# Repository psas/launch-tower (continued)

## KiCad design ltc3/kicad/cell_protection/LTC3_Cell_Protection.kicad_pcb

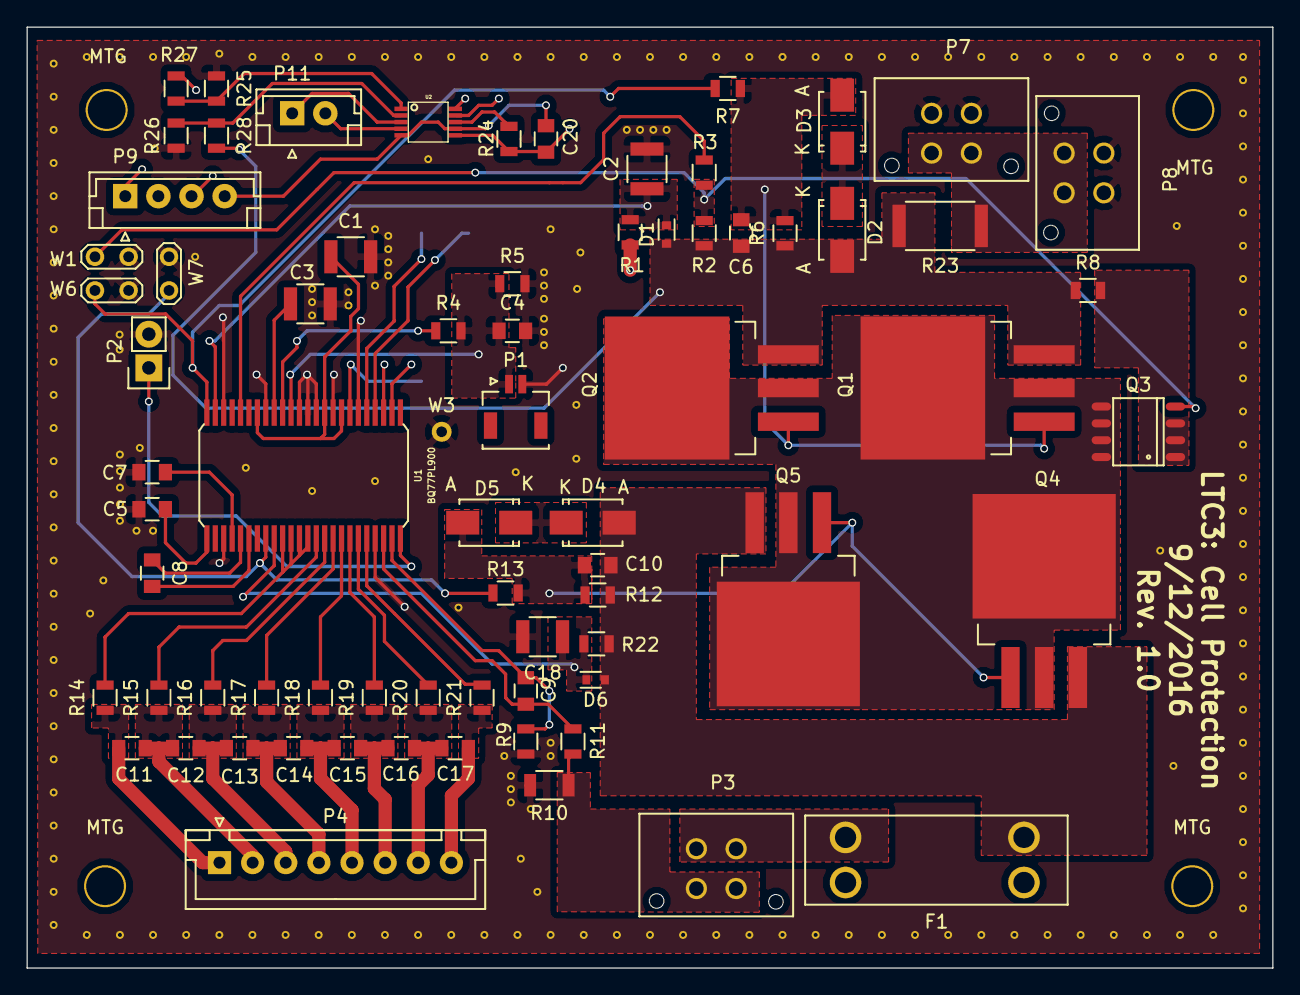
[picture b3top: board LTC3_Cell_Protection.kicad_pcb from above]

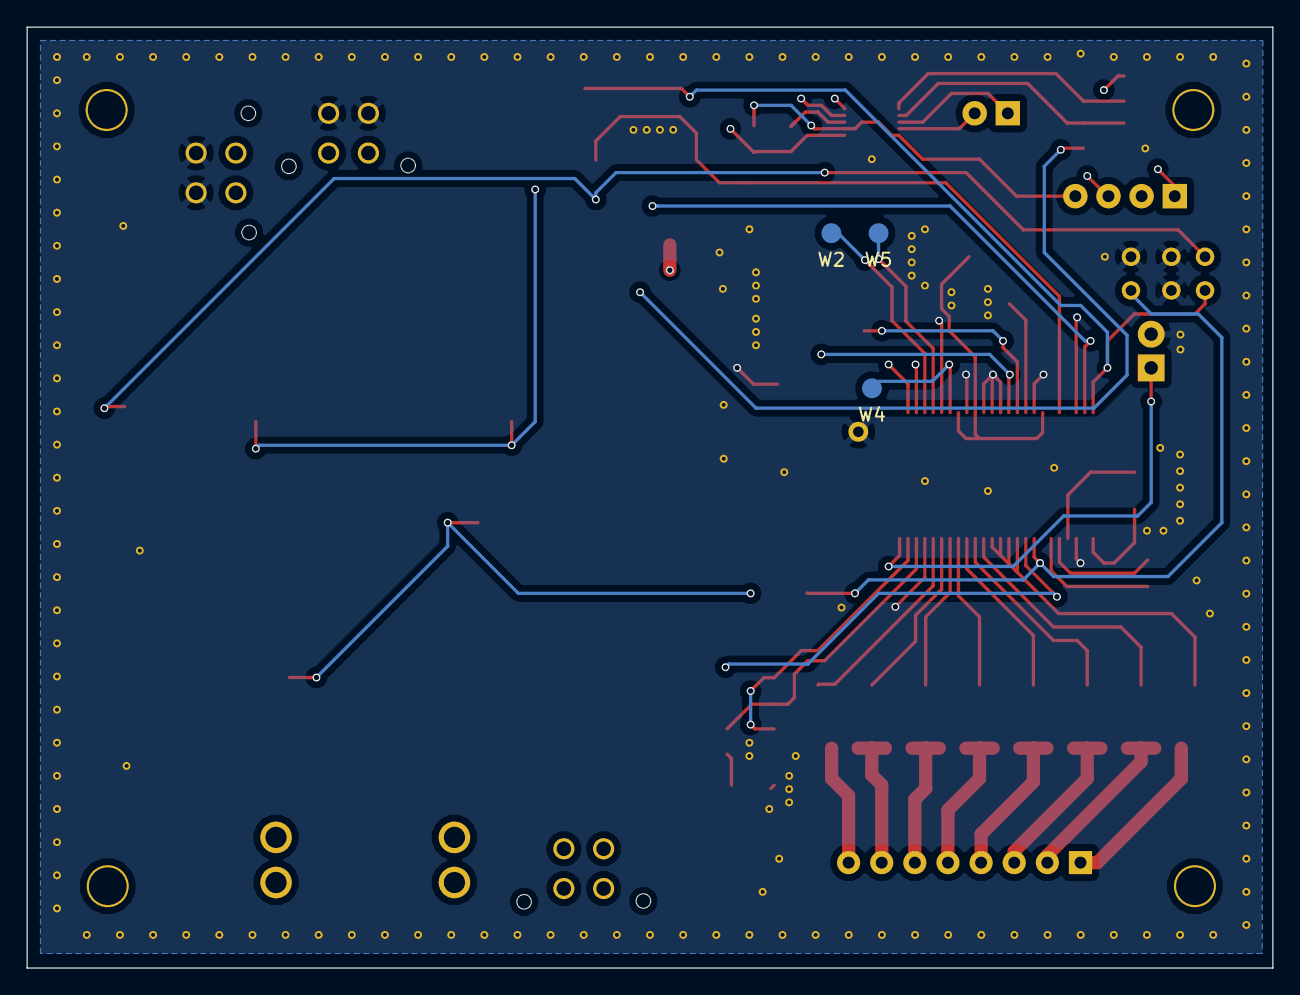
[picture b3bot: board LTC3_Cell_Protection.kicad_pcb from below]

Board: 4 copper layers, 94.0 x 71.0 mm, 80 parts (3 on the bottom side), 57 nets.

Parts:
C1, C2, C3, C18: 2.2μ; C_1210
C4: 10n; C_0805
C5: 4.7μ; C_0805
C6, C10: 4.7n; C_0805
C7, C8: 1μ; C_0805
C9, C11, C12, C13, C14, C15, C16, C17, C20: 0.1μ; C_0805
D1, D6: CDSU4148; SOD-523
D2, D3, D4, D5: SMAZ16; SMA_Standard
F1: 10A; Fuseholder_Auto_Blade_Regular_Keystone_3557-2
MTG: MountingHole_0.1120in_#4; MountingHole_0.1120in_number4
MTG#2, MTG#3, MTG#4: MountingHole_0.1120in_#4; MountingHole_0.1120in_number4
P1: XH header; JST_SHL_SM02B-SHLS-TF_02x1.00mm_Angled
P2: pin header; Pin_Header_Straight_1x02
P3, P7, P8: XH header; Molex_Microfit3_Header_02x02_Straight_43045-0428
P4: XH header; JST_XH_B08B-XH-A_08x2.50mm_Straight
P9: XH header; JST_EH_B04B-EH-A_04x2.50mm_Straight
P11: XH header; JST_EH_B02B-EH-A_02x2.50mm_Straight
Q1, Q2, Q4, Q5: SUM110P08-11; TO-263-3Lead
Q3: NDS9407; SO-8
R1: 10k; R_0805
R2: 390k; R_0805
R3: 820k; R_0805
R4: 6.98k; R_0805
R5: 61.9k; R_0805
R6, R12: 1M; R_0805
R7, R13: 1k; R_0805
R8: 1.78k; R_0805
R9, R11: 200; R_0805
R10: 1m; R_1206
R14, R15, R16, R17, R18, R19, R20, R21: 510; R_0805
R22: 100k; R_0805
R23: 60m; R_2512
R24: 5.6k; R_0805
R25, R26: 12k; R_0805
R27, R28: 75k; R_0805
U1: BQ77PL900
U2: LTC2990; MSOP-10
W1, W6, W7: TEST; Test_Point_2Pads
W2, W4, W5: TEST_1P; Measurement_Point_Round-SMD-Pad_Small
W3: TEST_1P; Measurement_Point_Round-TH_Small

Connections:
/I2C_CLK: P9.2, U1.27, U2.6
/I2C_DATA: P9.3, U1.26, U2.7
/VBATT: P7.3, P7.4, P8.3, P8.4, R1.1, R23.2, R27.2
GND: C1.2, C2.2, C3.2, C4.2, C5.2, C7.2, C18.2, P1.2, P2.2, P7.1, P7.2, P8.1, P8.2, R5.2, R9.2, R10.1, R25.1, R26.1, U1.3, U1.21, U1.30, U1.33, U1.35, U1.36, U1.37, U1.41, U1.46, W1.2, W3.1, W6.2, W7.2
GNDREF: C20.2, P9.4, U2.5, U2.9
unnamed: C1.1, U1.32, U1.34, U1.42
unnamed: C2.1, D1.1, R1.2, U1.47
unnamed: C3.1, U1.40
unnamed: C4.1, P1.1, R4.2, R5.1, U1.38
unnamed: C5.1, U1.1
unnamed: C6.1, D1.2, D2.2, Q1.3, Q2.3, R2.1, R6.1, R8.1, R23.1, R28.2
unnamed: C6.2, D3.2, Q1.1, Q2.1, R6.2, R7.1
unnamed: C7.1, U1.4
unnamed: C8.1, U1.5
unnamed: C8.2, U1.6
unnamed: C9.1, R9.1, U1.23
unnamed: C9.2, R11.1, U1.22
unnamed: C10.1, D4.2, D6.2, F1.1, Q4.3, Q5.3, R12.1, R22.1
unnamed: C10.2, D5.2, Q4.1, Q5.1, R12.2, R13.1
unnamed: C11.1, P4.1, R14.1
unnamed: C11.2, C12.1, P4.2, R15.1
unnamed: C12.2, C13.1, P4.3, R16.1
unnamed: C13.2, C14.1, P4.4, R17.1
unnamed: C14.2, C15.1, P4.5, R18.1
unnamed: C15.2, C16.1, P4.6, R19.1
unnamed: C16.2, C17.1, P4.7, R20.1
unnamed: C17.2, P4.8, R21.1
unnamed: C18.1, D6.1, R22.2, U1.9
unnamed: C20.1, P9.1, R24.1, U2.10
unnamed: D2.1, D3.1
unnamed: D4.1, D5.1
unnamed: F1.2, P3.1, P3.2
unnamed: P2.1, U1.24
unnamed: P3.3, P3.4, R10.2, R11.2
unnamed: P11.1, U2.3
unnamed: P11.2, U2.4
unnamed: Q1.2, Q1.4, Q2.2, Q2.4, Q3.5, Q3.6, Q3.7, Q3.8, Q4.2, Q4.4, Q5.2, Q5.4
unnamed: Q3.1, Q3.2, Q3.3, R8.2
unnamed: Q3.4, R2.2, R3.1, W1.1
unnamed: R3.2, U1.44
unnamed: R4.1, U1.39
unnamed: R7.2, U1.48, W6.1
unnamed: R13.2, U1.8, W7.1
unnamed: R14.2, U1.10, U1.11, U1.12, U1.13
unnamed: R15.2, U1.14
unnamed: R16.2, U1.15
unnamed: R17.2, U1.16
unnamed: R18.2, U1.17
unnamed: R19.2, U1.18
unnamed: R20.2, U1.19
unnamed: R21.2, U1.20
unnamed: R24.2, U2.8
unnamed: R25.2, R27.1, U2.1
unnamed: R26.2, R28.1, U2.2
unnamed: U1.28, W2.1
unnamed: U1.29, W5.1
unnamed: U1.31, W4.1

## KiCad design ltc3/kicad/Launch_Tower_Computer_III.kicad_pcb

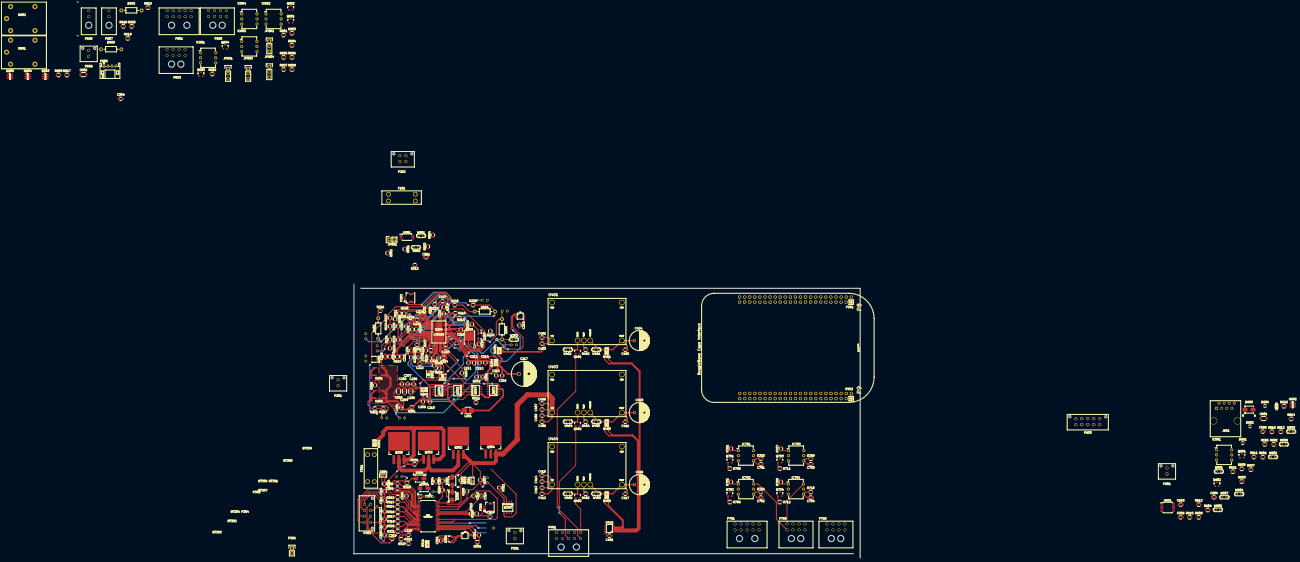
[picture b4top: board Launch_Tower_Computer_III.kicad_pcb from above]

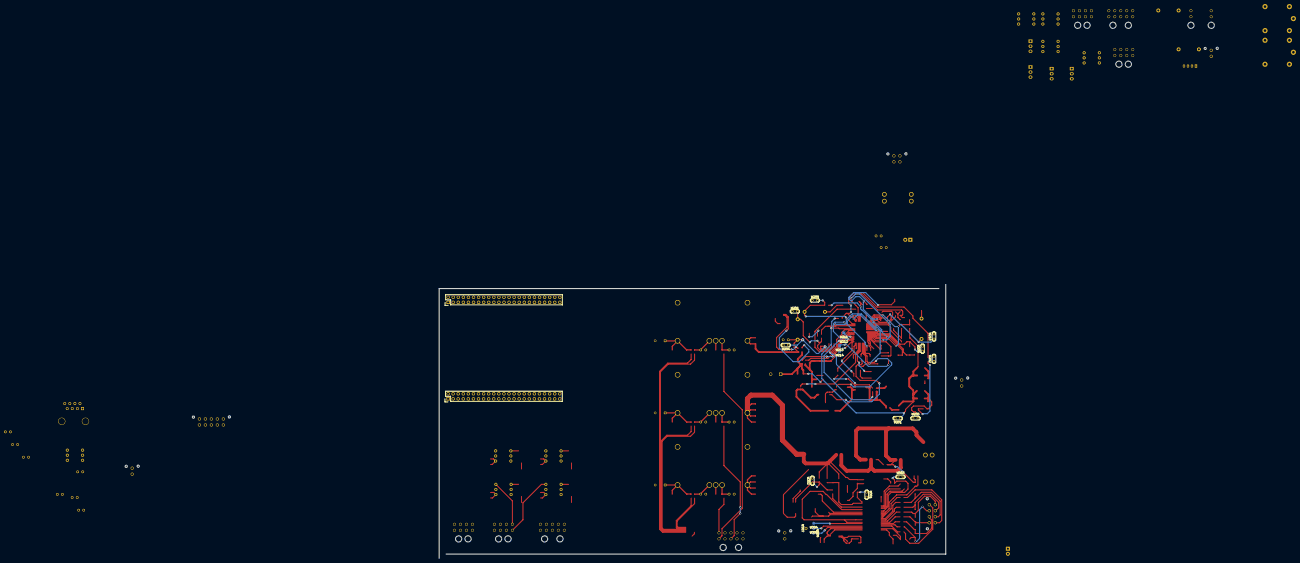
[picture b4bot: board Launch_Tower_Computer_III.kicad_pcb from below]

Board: 2 copper layers, 253.4 x 137.1 mm, 349 parts (21 on the bottom side), 234 nets.

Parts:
BT301, BT302, BT303, BT304, BT305, BT306, BT307, BT308: Dummy_Empty
C201, C202: 470n; C_0805
C203, C204, C205: 33µ; C_1206
C206, C207, C208, C209, C210, C218: 2.2µ; C_0805
C211, C212, C229: 4.7µ; C_0805
C213, C308, C309, C402, C405, C411, C417, C604, C701, C702, C703, C704: 1μ; C_0805
C214, C228, C230: 100n; C_0805
C215, C216: 10μ; C_0805
C217: 150μ; C_Radial_D12.5_L25_P5
C219, C301, C310, C311, C312, C315, C317, C318, C319, C320, C401, C501, C603, C605, C606: 0.1μ; C_0805
C220, C222: 4.7u; C_0805
C221, C225: 1n; C_0805
C223, C224: 220n; C_0805
C226: 0.18µ; C_0805
C227: 1µ; C_0805
C231, C233, C316: 10n; C_0805
C232: 0.33µ; C_0805
C234: 8.2n; C_0805
C235: 220p; C_0805
C236: 68n; C_0805
C302: 470p; C_0805
C303, C304: 4.7n; C_0805
C305, C306, C313, C314, C403: 2.2μ; C_0805
C307, C406, C407, C408, C409, C412, C413, C414, C415: 4.7μ; C_0805
C404, C410, C416: 470μ; C_Radial_D10_L25_P5
C601: 10μ; C_1206
C602: NP; C_1206
D201, D202: CMMR1U-02; SOD-123
D203: 1N4743A; Choke_Horizontal_RM10mm
D204, D205, D603, D605: LED; Choke_Horizontal_RM10mm
D301, D304: 1SS355; TUMD2
D302, D303, D305, D306: SMAZ16; SMA_Standard
D601, D602, D604: CDSU4148; R_0603
D609: 3.3V; SMA_Standard
F201: 15A; Fuseholder_Auto_Blade_Regular_Keystone_3557-2
F301: 10A; Fuseholder_Auto_Blade_Regular_Keystone_3557-2
IC601, IC701, IC702, IC703, IC704, IC801, IC802, IC803, IC804: TLP3542; DIP-6_W7.62mm
J601: RJ45; RJ45_8
JP501: WR_ENABLE; Pin_Header_Straight_1x02
JP801, JP802, JP803, JP804: Trigger Level; Pin_Header_Straight_1x03
K601, K602: RELAY_1C; G5LE-14
L201: 10µH; Inductor_1212
P201: PV_IN; Molex_Microfit3_Header_02x01_Straight_43045-0228
P202: LAB_IN; Molex_Microfit3_Header_02x02_Straight_43045-0428
P203, P305: S2BPHKS; JST_SHL_SM02B-SHLS-TF_02x1.00mm_Angled
P301: CONN_BATT_MAIN; Molex_Microfit3_Header_02x01_Straight_43045-0228
P302, P304: Dummy_Empty
P303: CONN_BATT_SENSE; Molex_Microfit3_Header_02x04_Straight_43045-0828
P306: PIN_HEAD_1x2; Pin_Header_Straight_1x02
P401, P701, P801: 43045-1000; Molex_Microfit3_Header_02x05_Angled_43045-100x
P501: BeagleBone_Black_Expansion_Header_P8; Pin_Header_Straight_2x23
P502: BeagleBone_Black_Expansion_Header_P9; Pin_Header_Straight_2x23
P601: BATT-IN; Molex_Microfit3_Header_02x01_Straight_43045-0228
P603: UMBILICAL; Molex_Microfit3_Header_02x05_Straight_43045-1028
P605, P607: 43045-0200; Molex_Microfit3_Header_02x01_Angled_43045-020x
P606: S4B-PH-K; JST_PH_S4B-PH-K_04x2.00mm_Angled
P608: 43025-0200; Molex_Microfit3_Header_02x01_Straight_43045-0228
P703, P705, P803, P805: 43045-0800; Molex_Microfit3_Header_02x04_Angled_43045-080x
Q201, Q202, Q203, Q204: BSC028N06NS; SO-8
Q205: ZVN4525E6; SOT-26
Q206: ZVP3310F; PG-TDSON-8
Q207: MMBT5550L; SOT-23
Q301: MMBT3904; SOT-23
Q302, Q303, Q304, Q305: SUM110P08-11; TO-263-3Lead
Q306: NDS9407; SO-8
Q401, Q402, Q403: BSS138; SOT-23
Q601, Q602, Q701, Q702, Q703, Q704, Q801, Q802, Q803, Q804: PMV45EN; SOT-23
Q603, Q604, Q605: ZVN4525E6; SOT-23-6
R201, R202, R210, R213: 10; R_0805
R203, R204: 5m; CST0612
R205, R302: 30m; CST0612
R206, R207, R208, R209, R212: 0; R_0805
R211: 5m; R_0805
R214: 196k; R_0805
R215, R217, R236, R303, R601, R605, R608, R615, R622, R705, R706, R711, R712, R803, R804, R807, R808: 10k; R_0805
R216: 8.06k; R_0805
R218, R306, R604, R614: 100k; R_0805
R219: 294k; R_0805
R220, R223: 11.5k; R_0805
R221: 57.6k; R_0805
R222: 10.2k; R_0805
R224: 93.1k; R_0805
R225: 26.1k; R_0805
R226: 215k; R_0805
R227: 7.68k; R_0805
R228: 16.5k; R_0805
R229, R402: 21k; R_0805
R230, R238: 3.32k; R_0805
R231: 27.1k; R_0805
R232: 3.01k; R_0805
R233: 110k; R_0805
R234: 1.3k; R_0805
R235: 243k; R_0805
R237: 53.6k; R_0805
R239: 35.7k; R_0805
R240, R241: 549; R_0805
R242: 200k; R_0805
R301, R501, R502, R503, R504, R612: 5.6k; R_0805
R304, R305: 1M; R_0805
R307: 390k; R_0805
R308: 820k; R_0805
R309, R310: 1k; R_0805
R311: 1.78k; R_0805
R312, R313, R314, R316, R317, R319, R320, R321: 500; R_0805
R315: 6.89k; R_0805
R318: 61.9k; R_0805
R322, R323: 200; R_0805
R324: 1m; CST0612
R401: 0.1; CST0612
R403, R405: 60m; CST0612
R404, R406: 2.91k; R_0805
R602: 120; R_0805
R603, R611: 62k; R_0805
R606: 100; R_0805
R607: 500k; R_0805
R609: NP; R_0805
R610, R620: 250; R_0805
R613: 1.5k; R_0805
R616, R621: 5.1k; R_0805
R617, R618, R619: 30k; R_0805
R701, R702, R707, R708, R801, R802, R805, R806: 270; R_0805
R703, R704, R709, R710: 51k; R_0805
U201, U202: PI2127; LGA-17
U203, U301: LTC2990; MSOP-10
U204: LT8490
U302: BQ77PL900
U401: PTN78020W
U402: LTC2991; MSOP-16
U403, U404: PTN78020H; PTN78020W
U501: 24C256; TSSOP-8_4.4x3mm_Pitch0.65mm
U601: CD74HC14; TSSOP-14_4.4x5mm_Pitch0.65mm
U602: SN65220DBV; SOT-23-6
U603: 741G08; SOT-353
W201, W202, W203, W204, W205, W206, W208, W209, W210, W301, W302, W303, W401, W402, W403, W404, W405, W406, W501, W502: TEST; Test_Point_2Pads
W211, W212, W213, W214: TEST_1P; Measurement_Point_Square-SMD-Pad_Small
W304, W305, W306: TEST_1P; Measurement_Point_Round-SMD-Pad_Small
W307: TEST_1P; Measurement_Point_Round-TH_Small
W601: 14.8-16.8V; Test_Point_2Pads
W602, W603, W604, W605, W606: 0/5V; Test_Point_2Pads
W607: 0/3.3V; Test_Point_2Pads

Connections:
+3V3: C227.1, C229.1, P401.2, P401.5, P401.8, R223.1, R234.1, R238.1, U204.4, U204.14, U204.58
+5V: C219.1, C301.1, C401.1, C501.1, C605.1, C606.1, D601.1, D604.1, JP801.1, JP802.1, JP803.1, JP804.1, P502.5, P502.6, Q603.1, Q604.1, Q605.1, R301.1, R401.1, R501.1, R502.1, R503.1, R504.1, R601.1, R616.1, R701.1, R702.1, R707.1, R708.1, R801.1, R802.1, R805.1, R806.1, U203.10, U301.10, U401.5, U402.16, U501.8, U601.14, W401.2
+12V: P705.1, P705.3, P705.5, P705.7, R403.1, U403.5, W403.2
+19V: P603.1, R405.1, R612.2, U404.5, W405.2
/12V_ENn: P401.4, P502.23
/19V_ENn: P401.7, P502.27
/BeagleBone Black Cape/BQ_XALERT: P501.23, U302.25
/BeagleBone Black Cape/ROCKET_IGNITE: P502.15, Q602.1, R620.1, R622.1, W607.1
/DC-DC Converters/5V_INHIBIT_FET: P401.1, Q401.1
/DC-DC Converters/12V_INHIBIT_FET: P401.3, Q402.1
/DC-DC Converters/19V_INHIBIT_FET: P401.6, Q403.1
/EXT_TRG_EN_1: P501.35, Q801.1, R803.1
/EXT_TRG_EN_2: P501.33, Q802.1, R804.1
/EXT_TRG_EN_3: P501.31, Q803.1, R807.1
/EXT_TRG_EN_4: P501.32, Q804.1, R808.1
/External Device Power/EXT_POW_1_FET_D: P701.1, Q701.3
/External Device Power/EXT_POW_1_LED_CATH: IC701.2, P701.2
/External Device Power/EXT_POW_1_OPTO_RELAY_P: IC701.6, P705.2
/External Device Power/EXT_POW_2_FET_D: P701.3, Q702.3
/External Device Power/EXT_POW_2_LED_CATH: IC702.2, P701.4
/External Device Power/EXT_POW_2_OPTO_RELAY_P: IC702.6, P705.4
/External Device Power/EXT_POW_3_FET_D: P701.5, Q703.3
/External Device Power/EXT_POW_3_LED_CATH: IC703.2, P701.6
/External Device Power/EXT_POW_3_OPTO_RELAY_P: IC703.6, P705.6
/External Device Power/EXT_POW_4_FET_D: P701.7, Q704.3
/External Device Power/EXT_POW_4_LED_CATH: IC704.2, P701.8
/External Device Power/EXT_POW_4_OPTO_RELAY_P: IC704.6, P705.8
/External Device Triggers/EXT_TRG_1_FET_D: P801.1, Q801.3
/External Device Triggers/EXT_TRG_1_LED_CATH: IC801.2, P801.2
/External Device Triggers/EXT_TRG_1_OPTO_RELAY: IC801.6, P803.2
/External Device Triggers/EXT_TRG_2_FET_D: P801.3, Q802.3
/External Device Triggers/EXT_TRG_2_LED_CATH: IC802.2, P801.4
/External Device Triggers/EXT_TRG_2_OPTO_RELAY: IC802.6, P803.4
/External Device Triggers/EXT_TRG_3_FET_D: P801.5, Q803.3
/External Device Triggers/EXT_TRG_3_LED_CATH: IC803.2, P801.6
/External Device Triggers/EXT_TRG_3_OPTO_RELAY: IC803.6, P803.6
/External Device Triggers/EXT_TRG_4_FET_D: P801.7, Q804.3
/External Device Triggers/EXT_TRG_4_LED_CATH: IC804.2, P801.8
/External Device Triggers/EXT_TRG_4_OPTO_RELAY: IC804.6, P803.8
/GPIO_EXT_PWR_1: Q701.1, R705.1
/GPIO_EXT_PWR_2: Q702.1, R706.1
/GPIO_EXT_PWR_3: Q703.1, R711.1
/GPIO_EXT_PWR_4: Q704.1, R712.1
/I2C_CLOCK: P502.19, R503.2, U203.7, U301.7, U302.27, U402.11, U501.6, W502.1
/I2C_DATA: P502.20, R504.2, U203.6, U301.6, U302.26, U402.10, U501.5, W501.1
/IGN_RTL: P501.22, P501.29, R611.2, R614.1
/Power In, Charge Controller/BG1: Q203.4, U204.23
/Power In, Charge Controller/BG2: Q204.4, R208.1
/Power In, Charge Controller/EXTVCC: C202.2, C211.1, C212.1, C213.1, C214.1, Q202.5, R204.2, U204.40
/Power In, Charge Controller/SW1: C223.1, L201.1, Q201.3, Q203.5, U204.31
/Power In, Charge Controller/SW2: C224.1, L201.2, Q202.3, Q204.5, U204.29
/Power In, Charge Controller/TG1: Q201.4, R207.2
/Power In, Charge Controller/TG2: Q202.4, U204.28
/ROCKET_READYn: P501.25, R603.1, R604.2
/Rocket Umbilical & Ignition Control/IGN_BATT_P: P601.1, W601.2
/Rocket Umbilical & Ignition Control/ROCKET_ETH_1: J601.3, P603.3
/Rocket Umbilical & Ignition Control/ROCKET_ETH_2: J601.4, P603.4
/Rocket Umbilical & Ignition Control/ROCKET_ETH_3: J601.5, P603.5
/Rocket Umbilical & Ignition Control/ROCKET_ETH_4: J601.6, P603.6
/Rocket Umbilical & Ignition Control/ROCKET_READY_5V: P603.2, R602.2, U602.4, U602.6, W602.1
/Rocket Umbilical & Ignition Control/UMB_CONN_FROM_RKT: D609.1, P603.7, R621.2
/UMB_CONn: C604.1, P501.24, P501.27, R616.2, R621.1
GND: C203.2, C204.2, C205.2, C206.2, C207.2, C208.2, C209.2, C210.2, C211.2, C212.2, C213.2, C214.2, C215.2, C216.2, C217.2, C218.2, C219.2, C220.2, C221.2, C222.2, C225.2, C226.2, C227.2, C228.2, C229.2, C230.2, C231.2, C232.2, C233.2, C234.2, C235.2, C236.2, C301.2, C305.2, C306.2, C307.2, C308.2, C313.2, C314.2, C316.2, C401.2, C402.2, C403.2, C404.2, C405.2, C406.2, C407.2, C408.2, C409.2, C410.2, C411.2, C412.2, C413.2, C414.2, C415.2, C416.2, C417.2, C501.2, C601.2, C602.2, C603.2, C604.2, C605.2, C606.2, C701.2, C702.2, C703.2, C704.2, D603.1, D605.1, D609.2, IC601.2, IC601.4, JP501.2, JP801.3, JP802.3, JP803.3, JP804.3, P201.1, P202.1, P203.2, P305.2, P306.2, P401.9, P401.10, P501.1, P501.2, P502.1, P502.2, P502.43, P502.44, P502.45, P502.46, P603.8, P603.9, P603.10, P606.4, P701.9, P701.10, P703.2, P703.4, P703.6, P703.8, P801.9, P801.10, P805.2, P805.4, P805.6, P805.8, Q205.4, Q401.2, Q402.2, Q403.2, Q601.2, Q602.2, Q701.2, Q702.2, Q703.2, Q704.2, Q801.2, Q802.2, Q803.2, Q804.2, R206.2, R211.2, R212.2, R213.2, R216.2, R217.2, R222.2, R225.2, R226.1, R227.2, R229.2, R235.2, R239.2, R240.2, R241.2, R242.2, R318.2, R324.1, R402.2, R404.2, R406.2, R604.1, R605.2, R608.2, R613.2, R614.2, R615.2, R617.2, R618.2, R619.2, R622.2, R703.2, R704.2, R705.2, R706.2, R709.2, R710.2, R711.2, R712.2, R803.2, R804.2, R807.2, R808.2, U201.6, U202.6, U203.5, U203.8, U203.9, U204.9, U204.21, U204.55, U204.59, U204.61, U204.62, U204.63, U301.5, U301.9, U302.3, U302.21, U302.30, U302.33, U302.35, U302.36, U302.37, U302.41, U302.46, U401.1, U401.7, U402.9, U402.13, U402.14, U402.15, U403.1, U403.7, U404.1, U404.7, U501.1, U501.2, U501.4, U601.7, U602.2, U602.5, W201.2, W202.2, W203.2, W204.2, W205.1, W206.2, W208.2, W209.2, W210.2, W301.2, W302.2, W303.2, W307.1, W401.1, W402.1, W403.1, W404.1, W405.1, W406.1, W501.2, W502.2, W602.2, W603.2, W604.2, W605.2, W606.2, W607.2
GND_IGN: P601.2, P607.2, W601.1
unnamed: C201.1, R201.2
unnamed: C202.1, R202.2
unnamed: C209.1, C210.1, Q201.5, R201.1, R203.1
unnamed: C215.1, C216.1, C217.1, R202.1, R204.1, R205.2
unnamed: C220.1, C222.1, R209.1, U204.7, U204.24
unnamed: C221.1, R210.1, U204.13
unnamed: C223.2, D201.1, U204.33
unnamed: C224.2, D202.1, U204.27
unnamed: C225.1, R213.1, U204.12
unnamed: C226.1, R220.1, R221.2
unnamed: C228.1, U204.19
unnamed: C230.1, P203.1, R223.2, U204.3
unnamed: C231.1, R229.1, U204.10, U204.53
unnamed: C232.1, R228.2, R230.2
unnamed: C233.1, R231.2, R232.2, R235.1, U204.17
unnamed: C234.1, R236.2
unnamed: C235.1, R236.1, U204.18
unnamed: C236.1, R237.2, U204.56
unnamed: C302.1, Q301.1, Q301.2, U301.3
unnamed: C302.2, Q301.3, U301.4
unnamed: C303.2, D305.2, Q302.1, Q304.1, R304.2, R309.1
unnamed: C304.1, D303.2, D304.2, Q303.3, Q305.3, R302.2, R305.1, R306.1
unnamed: C304.2, D306.2, Q303.1, Q305.1, R305.2, R310.1
unnamed: C305.1, D301.1, R303.2, U302.47
unnamed: C306.1, D304.1, R306.2, U302.9
unnamed: C307.1, U302.1
unnamed: C308.1, U302.4
unnamed: C309.1, U302.5
unnamed: C309.2, U302.6
unnamed: C310.1, P303.1, R312.1
unnamed: C310.2, C311.1, P303.2, R313.1
unnamed: C311.2, C312.1, P303.3, R314.1
unnamed: C312.2, C315.1, P303.4, R316.1
unnamed: C313.1, U302.32, U302.34, U302.42
unnamed: C314.1, U302.40
unnamed: C315.2, C317.1, P303.5, R317.1
unnamed: C316.1, P305.1, R315.2, R318.1, U302.38
unnamed: C317.2, C318.1, P303.6, R319.1
unnamed: C318.2, C319.1, P303.7, R320.1
unnamed: C319.2, P303.8, R321.1
unnamed: C320.1, R322.1, U302.22
unnamed: C320.2, R323.1, U302.23
unnamed: C404.1, C405.1, R401.2, U401.6
unnamed: C410.1, C411.1, R403.2, U403.6
unnamed: C416.1, C417.1, R405.2, U404.6
unnamed: C601.1, C602.1, R606.1, R607.1, R609.1, U601.9, W606.1
unnamed: C603.1, R612.1, R613.1, U601.13, W603.1
unnamed: C701.1, IC701.4, P703.1, R703.1
unnamed: C702.1, IC702.4, P703.3, R704.1
unnamed: C703.1, IC703.4, P703.5, R709.1
unnamed: C704.1, IC704.4, P703.7, R710.1
unnamed: D201.2, D202.2, R209.2
unnamed: D203.2, Q206.2, Q207.2, R218.2, W206.1
unnamed: D204.1, R240.1
unnamed: D204.2, R234.2, U204.51, W209.1
unnamed: D205.1, R241.1
unnamed: D205.2, R238.2, U204.2, W210.1
unnamed: D302.1, D305.1
unnamed: D303.1, D306.1
unnamed: D601.2, Q601.3
unnamed: D602.1, R607.2, R609.2, U603.3
unnamed: D602.2, R606.2
unnamed: D603.2, R610.2
unnamed: D604.2, Q602.3
unnamed: D605.2, R620.2
unnamed: F201.1, P202.2
unnamed: F201.2, R215.1, U202.12, U202.13, U202.14, U202.15, U202.16, W205.2
unnamed: F301.1, R302.1
unnamed: F301.2, P301.1
unnamed: IC601.1, R602.1
unnamed: IC601.6, R601.2, U601.1
unnamed: IC701.1, R701.2
unnamed: IC702.1, R702.2
unnamed: IC703.1, R707.2
unnamed: IC704.1, R708.2
unnamed: IC801.1, R801.2
unnamed: IC801.4, P805.1
unnamed: IC802.1, R802.2
unnamed: IC802.4, P805.3
unnamed: IC803.1, R805.2
unnamed: IC803.4, P805.5
unnamed: IC804.1, R806.2
unnamed: IC804.4, P805.7
unnamed: JP501.1, R501.2, U501.7
unnamed: JP801.2, P803.1
unnamed: JP802.2, P803.3
unnamed: JP803.2, P803.7
unnamed: JP804.2, P803.5
unnamed: Q603.3, R617.1
unnamed: P605.1, Q604.3, R618.1
unnamed: P201.2, U201.12, U201.13, U201.14, U201.15, U201.16, W202.1
unnamed: P301.2, R324.2
unnamed: P306.1, U302.24
unnamed: P605.2, P607.1, Q605.3, R619.1
unnamed: P606.1, Q603.4
unnamed: P606.2, Q604.4
unnamed: P606.3, Q605.4
unnamed: Q203.3, Q204.3, R210.2, R211.1
unnamed: Q205.1, R214.2, R216.1, U204.54
unnamed: Q205.3, R215.2, R217.1
unnamed: Q206.1, R219.1
unnamed: Q207.1, R242.1, U204.8, U204.49
unnamed: Q207.3, R225.1
unnamed: Q302.2, Q303.2, Q304.2, Q305.2, Q306.5
unnamed: Q306.3, R311.2
unnamed: Q306.4, R307.2, R308.1, W302.1
unnamed: Q401.3, U401.3, W402.2
unnamed: Q402.3, U403.3, W404.2
unnamed: Q403.3, U404.3, W406.2
unnamed: Q601.1, R608.1, U601.6
unnamed: R203.3, U204.44
unnamed: R203.4, U204.45
unnamed: R204.3, U204.41
unnamed: R204.4, U204.42
unnamed: R205.3, U203.2
unnamed: R205.4, U203.1
unnamed: R206.1, U201.2
unnamed: R207.1, U204.32
unnamed: R208.2, U204.25
unnamed: R212.1, U202.2
unnamed: R219.2, R221.1, R222.1, U204.16, U204.57
unnamed: R220.2, U204.5
unnamed: R224.2, R227.1, R228.1, U204.1, U204.15
unnamed: R226.2, U204.22
unnamed: R230.1, U204.6
unnamed: R231.1, U204.50
unnamed: R232.1, U204.64
unnamed: R233.2, R239.1, U204.11, W208.1
unnamed: R237.1, U204.20
unnamed: R301.2, U301.8
unnamed: R302.3, U301.2
unnamed: R302.4, U301.1
unnamed: R308.2, U302.44
unnamed: R309.2, U302.48, W301.1
unnamed: R310.2, U302.8, W303.1
unnamed: R312.2, U302.10, U302.11, U302.12, U302.13
unnamed: R313.2, U302.14
unnamed: R314.2, U302.15
unnamed: R315.1, U302.39
unnamed: R316.2, U302.16
unnamed: R317.2, U302.17
unnamed: R319.2, U302.18
unnamed: R320.2, U302.19
unnamed: R321.2, U302.20
unnamed: R322.2, R324.3
unnamed: R323.2, R324.4
unnamed: R401.3, U402.2
unnamed: R401.4, U402.1
unnamed: R402.1, U401.4
unnamed: R403.3, U402.4
unnamed: R403.4, U402.3
unnamed: R404.1, U403.4
unnamed: R405.3, U402.6
unnamed: R405.4, U402.5
unnamed: R406.1, U404.4
unnamed: R502.2, U501.3
unnamed: R603.2, U601.4
unnamed: R605.1, U601.2, U601.3, U603.1, W604.1
unnamed: R610.1, R611.1, U601.10
unnamed: R615.1, U601.12, U603.2, W605.1
unnamed: U204.35, W214.1
unnamed: U204.36, W213.1
unnamed: U204.37, W212.1
unnamed: U204.38, W211.1
unnamed: U302.28, W306.1
unnamed: U302.29, W305.1
unnamed: U302.31, W304.1
unnamed: U601.5, U601.8, U601.11
VBATT: C303.1, C402.1, C403.1, C406.1, C407.1, C408.1, C409.1, C412.1, C413.1, C414.1, C415.1, D203.1, D301.2, D302.2, Q206.3, Q302.3, Q304.3, R205.1, R218.1, R303.1, R304.1, R307.1, R311.1, U401.2, U403.2, U404.2, W203.1, W204.1
VIN: C201.2, C203.1, C204.1, C205.1, C206.1, C207.1, C208.1, C218.1, R203.2, R214.1, R224.1, R233.1, U201.8, U201.9, U201.10, U201.11, U201.17, U202.8, U202.9, U202.10, U202.11, U202.17, U204.46, W201.1

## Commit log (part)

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2015-01-27 More edits to LTC3 requirements doc.
2015-02-01 Added beginning of LTC2 high-level diagram
2015-02-11 More work on LTC3 power diagram. Still a rough draft.
2015-03-15 Updated LTC3 README.
2015-04-02 More work on LTC3 schematic. 1. Created placeholder "power in" schematic. 2. First cut at external trigger schematic (MOSTFETs and mechanical relays).
2015-04-04 Incremental progress on LTC3 design spec, schematic.
2015-04-09 Another minor design spec correction.
2015-04-18 Updated datasheet collection. Added notes to schematic.
2015-04-25 Datasheet updates. 1. Deleted Cincon DC-DC converter datasheet. 2. Updated TDK-Lambda DC-DC converter datasheet. 3. Updated design spec with links to online TDK docs.
2015-05-16 Modified LTC3 Requirements: removed battery voltage requirement. Battery technology is (more or less) independent of the required power rails, and the team is strongly considering using a battery wit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
2015-05-16 Added some notes for LT8490 configuration
2015-05-30 Added BQ77PL9000 schematic and footprint to libs.
2015-06-10 Working space for charging circuit.
2015-06-13 Very minor adjustments to BeagleBone Cape schematic layout.
2015-06-19 Tidying up ltc3/kicad/ tree.
2015-07-01 More LTC3 design: completed DC-DC converter schematics. Mostly. A thorough review of the PTN78020[WH] datasheet followed by a once-over of the schematic wouldn't hurt.
2015-07-17 Changes in the ltc3/temp/ sub-tree. 1. Added a text file of LTC299x-related notes (I2C V/A/T sensor). 2. Deleted ltc3/temp/kernel-module-ltc2990. It was it's own git repo, and subprojects give me fit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
2015-07-24 Moved voltage/current sense resistors onto DC-DC Converter sheet. From the BeagleBone Cape sheet. This makes the schematics cleaner, as there are fewer hierarchical pins to keep track of.
2015-08-14 Added PDF schematic for LTC2 Eagle ignition board file. Changed name of component configuration docs.
2015-08-26 LTC3: Replaced incorrect EEPROM data sheet with the correct version.
2015-10-01 Added MSOP-16 footprint to ltc3 KiCad files.
2015-10-17 Baby steps towards formal LTC3 project planning.
2015-10-20 Progress on merging master with Charging_Circuit branch.
    Still have plenty of schematic clean-up to perform. There's a lot
    going on around the LT8490.
2015-10-25 Added TODO list to charging circuit page.
2015-10-31 Progress on cleaning up battery management and balance schematics.
2015-11-01 Deleted "Power Sources" sheet.
    Moved what little circuity it contained into the "Battery Charging"
    and "Battery Balancing" sheets.
2015-11-04 Added datasheets on weather/environment-resistant Ethernet connectors.
2015-11-07 LTC3: Renamed LT8705 datasheet file.
2015-11-08 LTC3: Added lab power input to batt mgmt schematic.
2015-11-14 LTC3: Mostly completed ignition control schematic.
2015-11-17 LTC3: Tidied up rocket interface schematic.
2015-11-22 Combined external power and trigger sheets.
    Still need to make the page pretty.
2015-11-22 LTC3: Added datasheet for TI bq77PL900 demo board.
    Contains a useful schematic of a working bq77-based circuit.
2015-11-22 LTC3: Renamed DC/DC converter-enabling hierachical pins.
2015-11-26 LTC3: Reordered schematic sub-sheets; updated PDF export of schematic.
    KiCad has an odd habit of ordering a schematic's sub-sheets without
    notice.
2015-12-12 LTC3: Minor edits to battery charging, balance sheets.
2015-12-15 LTC3: Minor cosmetic edits to rocket/ignition sheet.
2015-12-16 LTC3: Progress on rocket/ignition schematic.
    1. Fixed mis-wired relay diodes.
    2. Completed ignition relay circuitry.
    3. Began work on umbilical connector circuitry.
2015-12-16 LTC3: Progress on charging schematic.
    1. Merged Andy's updates to the battery charging schematic. Thanks,
    Andy!
    2. Re-annotated entire schematic; updated PDF.
2015-12-22 Added note section to heirarchical schematics. Added path to ground on DC-DC converters. Replaced thermistor with 'duct tape' 0 ohm resistor on BQL77PL900.
2015-12-29 LTC3: Began replacing Schottky OR diodes w/ "ideal" diodes.
    Created schematic symbol for TI LM74610-Q1 ideal/smart diode
    controller. Added relevant data sheets.
    Began implementing the circuitry that will replace the existing
    Schottky input diodes in the battery charging schematic. Left my work
    off to the left hand side of the page. Still need to complete and
    integrate with the charging circuitry.
2016-01-09 LTC3: More progress on prettifying the battery charger schematic.
2016-01-16 LTC3: Cleaned up battery charging and BeagleBone interface sheets.
2016-01-22 Deleted garbage file(s).
2016-01-30 LTC3: Replaced thermistor/0R on charger and balance schematics w/ connector.
    Each to be connected to an off-board NTC thermistor taped to the
    battery pack.
2016-02-07 LTC3: Minor adjustments, many comments from today's design review.
2016-02-10 LTC3: Updated PDF of schematic.
2016-02-13 LTC3: Deleted broken *cache.lib.
2016-02-17 Set all i2c on a single bus, added notes section, finished to do's, clarified important questions.
2016-02-19 LTC3: Standardized optoisolator selection.
    Replaced the Avago 4N35 on the ignition control schematic with the
    Toshiba TLP3542 used on the external power and triggers schematic.
    This reduces the number of unique parts used in the design. The Avago
    has an order of magnitude faster switching time than the Toshiba, but
    that shouldn't matter for the ignition control circuit; the Toshiba's
    2.5A max current is way more than sufficient.
2016-02-20 Updated DC-DC Converters and Beaglebone Sheets.
    *Added test points to both sheets.
    *Added a switch array for manual overrides on DC-DC converters page.
    *Removed finished ToDo's
2016-03-05 LTC3: Added rocket umbilical state detection to ignition sub-sheet.
2016-03-12 LTC3: Minor Changes to Battery Management -Removed unnecessary resistors on MOSFET gates -Added pin connector for EEPROM on BQ77PL900 -Changed resistor on LT8490 switch pins
2016-03-12 LTC3: Added test points; hid test point and ground symbol values.
    1. Added single-node test points to bq77PL900 VOUT and IOUT pins;
    included a ground test point nearby.
    2. Set all test point and ground symbols' value fields to invisible.
2016-03-26 LTC3: Deleted _autosave* file; updated .gitignore.
2016-04-02 LTC3: Fixed mis-oriented diodes in battery management schematic.
2016-04-11 Assigned component footprints.
2016-04-16 Really this time.
2016-04-16 LTC3: Minor fixes to test points in batt. balance schematic.
    Also updated netlist, schematic PDF.
2016-04-23 LTC3: Added off-board (front panel) connectors for external power and trigger circuits.
    Plus an inconsequential amount of PCB layout.
2016-04-30 LTC3: Schematic style policing and miscellaneous prettification.
    Completed all sheets but DC-DC converters and ignition control.
    Also updated netlist and schematic PDF export.
2016-05-08 LTC3: Fixes, clean-ups...
    1. Removed inverters from DC-DC converters' INHIBIT pin circuitry.
    Renamed node labels accordingly.
    2. Moved zero-volt charging FET on bq sheet. It was wired to bypass
    the discharge FETs, and should be bypassing the charge FETS.
    3. Added connectors between board and igntion external interfaces
    (breaker, arming switch, shorting bar, ignition power).
2016-05-09 LTC3: Minor cosmetic adjustment to ignition schematic.
2016-05-12 LTC3: More footprint assignment.
    Set footprint to "OFF-BOARD" for all off-board components. This
    results in an error dialog when opening the footprint assignment tool,
    but it makes it obvious which components shouldn't have any footprint
    assigned.
2016-05-15 LTC3: Reannotated schematic.
    Power nodes were mysteriously annotated incorrectly again.
2016-05-29 LTC3: Layout Work
    Guess what? More layout work! (still on the power section)
2016-06-08 LTC3: Made use of corrected bq footprint.
2016-06-15 LTC3: Added pin annotations to PTN78020[WH] footprint.
2016-06-16 LTC3: Fixed mis-named pin in VIN power node symbol.
2016-06-26 LTC3: Split single-board design into two boards.
    Separated the charge controller and cell protection circuitry onto its
    own board (kicad/charge_controller). The DC-DC converters,
    BeagleBone, external power and triggers, and ignition fire control
    circuitry remains together (kicad/ltc).
    Both boards have had their schematics updated. Sub-sheets for
    circuitry moved to the other board were removed. Still more work
2016-06-29 LTC3: Copied KiCad fp-lib-table into each board's sub-directory.
    Symlinks don't seem to work properly on Windows.
2016-06-29 LTC3: Moved the Coilcraft datasheet to the appropriate sub-directory.
2016-07-01 LTC3: LT8490 Layout
    Some final changes and preparation for LT8490 layout.
2016-07-06 LTC3: Layout Con't
    I spent like 5 minutes on this commit and got kind of frustrated. Not
    much in here.
2016-07-09 LTC3: Created footprint for mounting hole sized for a #4 screw.
2016-07-12 LTC3: Rev 0.1 of LTC3 Charge Controller Layout
    Finished new revision of LTC3 charge controller layout, featuring:
    -giant inductor footprint (squid)
    -mounting holes
    -thermal relief turned off for Vin
    -Vout connector
    -surface mount LEDs
2016-07-16 LTC3: Charge controller work.
    1. Added low-current DC rail connector (5V, 3.3V).
    2. Adde mfg name and part numbers for all resistors.
2016-07-16 LTC3: Layout Work/Connector Updating
    Added many needed connectors and added to layout.
    -Added 5V nodes for Charge Controller/Cell Protection
    -Added I2C bus connectors
    -Added Vin connectors for Cell Protection
    Added all connectors to layout and ensured all nodes were connected.
2016-07-22 LTC3: More LTC layout work
    Came to a rough finale of the LTC board layout.
2016-08-30 LTC3: More Charge Controller BOM selection.
2016-09-04 LTC3: Replaced DC-DC converters' individual switches with a single switch.
    One main power switch now enables all three converters.
    Added pin header to each converter's nINHIBIT pin to facilitate manual
    control.
2016-09-04 LTC3: Modified LTC DC-DC converter schematic.
    Added voltage dividers to both sides of LTC299x current sense
    resistors.
2016-09-04 LTC3: Modified LTC ignition control schematic.
    Gave ignition battery ground node a distinctive symbol.
2016-09-05 LTC3: Update to charge controller schematic/PCB
    -Adjusted resistors on charge controller for better current limiting
    -Changed footprints of current sense resistors
    -Began adjusting layout, making the board slightly larger
2016-09-06 LTC3: One last correction to charge controller BOM.
    And I'm serious this time.
2016-09-07 LTC3 Cell Protection Layout
    Reworked layout with changes to schematic and various footprints.
    Also added via stapling.
2016-09-08 LTC3 Cell Protection Layout
    A little bit of work on the silk screen for the board layout.
    We moved the temp sensing to off board, do we still want footprints for
    these on the cell protection board?
2016-09-08 LTC3: Minor changes to Charge Controller BOM.
    Nothing that impacts PCB layout.
2016-09-08 LTC3: Modified LTC BOM, schematic.
    1. Added footprints for mechanical relays. (PCB layout already had
    correct footprint; but incorrect annotation.)
    2. Created footprint for RJ-45 jack. This impacts the existing PCB
    layout.
2016-09-09 LTC3 Layout
    Minor changes to charge controller PCB.
2016-09-10 LTC3: Added mechanical drawing of Dialight LED indicators.
2016-09-13 LTC3: Doubled pin count of LTC's DC in and ignition battery connectors.
    Using the same 4-pin Molex MicroFit as used for battery connection on
    Charge Controller and Cell Protection boards.
2016-09-13 LTC3: LTC BOM and PCB changes.
    1. Added RJ45 connector outline to BeagleBone footprint.
    2. Rotated BeagleBone footprint on PCB, so that the RJ45 connector
    is on a board edge.
    3. Added a notch to the board for BeagleBone RJ45 jack clearance.
    4. Updated PCB footprint annotations to align with changes made to the
    LTC schematic in the past few months.
2016-09-15 LTC3: Some Pretty Dang Close Layout Updates
    It's working again, hooray! Pushing everything from the layout review
    yesterday. May give them a look over later this afternoon as well and
    export gerbers for the LTC board.
2017-02-09 Deleted old Gerber files.
2019-02-09 Updated LTC3 to-do list.
2019-03-08 Replaced old schematic PDFs with new KiCad v5 versions.
